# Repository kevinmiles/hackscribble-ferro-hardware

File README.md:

Hackscribble FRAM Hardware
==========================

#### *PCB designs for connecting Fujitsu MB85RS Ferroelectric memory (FRAM) to Arduino and LPCXpresso boards.*

Created on 20 April 2014 by Ray Benitez  
Last modified on 1 December 2014 by Ray Benitez		
  
These hardware designs are licensed by Ray Benitez under the Creative Commons Attribution-Sharealike 4.0 International License.
	
git@hackscribble.com | http://www.hackscribble.com | http://www.twitter.com/hackscribble

### About the hardware

#### Level converter circuits

These circuit snippets connect 3.3V MB85RS FRAM chips to 5V Arduino inputs / outputs.  

Two design approaches are shown:

1. Discrete design using BSS108 FETs, following the approach used by the Adafruit level converter.

2. Integrated design using TXB0104 to reduce PCB space required. 

The designs are in Eagle format.

#### Mini-shield

The mini-shield allows up to three 3.3V FRAMS to be connected to an Arduino (or an LPCXPresso board).  It uses an extended version of the integrated circuit snippet (above) using a TXB0108. The board has been tested with Arduino Uno and LPCXpresso 11U68 boards.

The design is in KiCad format.

The supply voltage for the Arduino / LPCXpresso side of the level converter is taken from the IOREF output of the Arduino / LPCXpresso.  This automatically adjusts for 3.3V or 5V boards.

The REVISION B board also includes test points for monitoring the SPI bus.
<br>

<hr>

### Change history

#### 1 December 2014

Added mini-shield REVISION C "slim" version.

#### 5 November 2014

Upgraded mini-shield to REVISION B.

#### 1 November 2014

Added mini-shield REVISION A.

#### 20 April 2014

Initial release of level converter circuits REVISION A.

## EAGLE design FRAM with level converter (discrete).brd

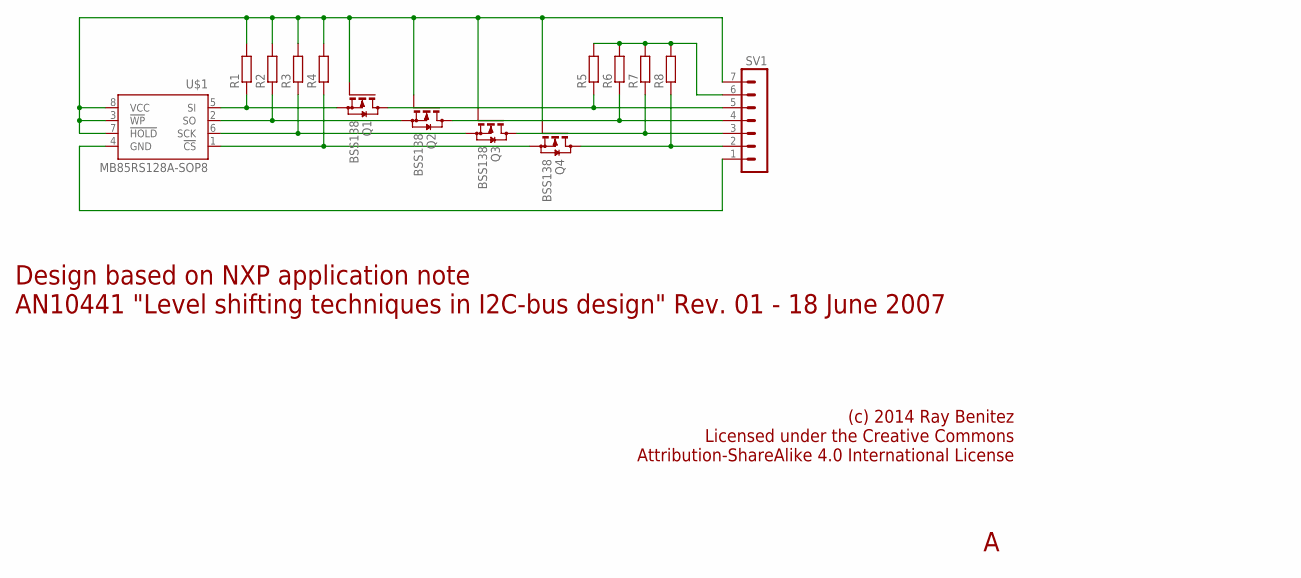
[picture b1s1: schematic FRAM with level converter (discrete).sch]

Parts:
Q1, Q2, Q3, Q4: BSS138; SOT23
R1, R2, R3, R4, R5, R6, R7, R8: R-EU_R0805; R0805
SV1: MA07-1
U$1: MB85RS128A-SOP8; SO08

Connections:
GND: SV1.1, U$1.4 (GND)
unnamed: Q1.2 (S), R1.1, U$1.5 (SI)
unnamed: Q2.2 (S), R2.1, U$1.2 (SO)
unnamed: Q3.2 (S), R3.1, U$1.6 (SCK)
unnamed: Q4.2 (S), R4.1, U$1.1 (!CS)
unnamed: Q1.1 (G), Q2.1 (G), Q3.1 (G), Q4.1 (G), R1.2, R2.2, R3.2, R4.2, SV1.7, U$1.3 (!WP), U$1.7 (!HOLD), U$1.8 (VCC)
unnamed: Q4.3 (D), R8.1, SV1.2
unnamed: Q3.3 (D), R7.1, SV1.3
unnamed: Q2.3 (D), R6.1, SV1.4
unnamed: Q1.3 (D), R5.1, SV1.5
unnamed: R5.2, R6.2, R7.2, R8.2, SV1.6

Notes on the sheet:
(c) 2014 Ray Benitez Licensed under the Creative Commons Attribution-ShareAlike 4.0 International License
Design based on NXP application note AN10441 "Level shifting techniques in I2C-bus design" Rev. 01 - 18 June 2007

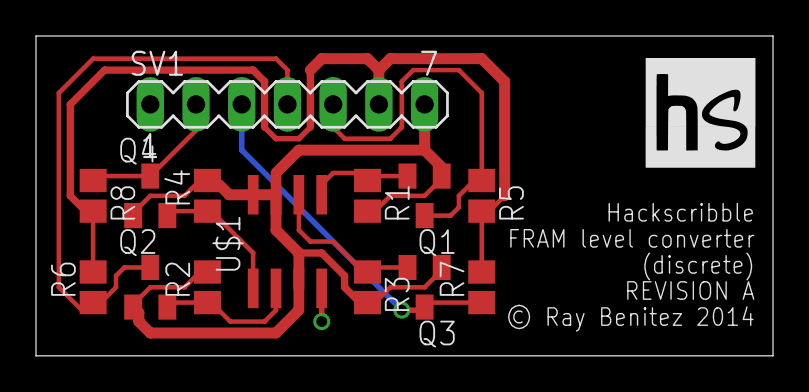
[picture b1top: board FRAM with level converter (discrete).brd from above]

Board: 2 copper layers, 40.9 x 17.8 mm, 14 parts (0 on the bottom side), 11 nets.

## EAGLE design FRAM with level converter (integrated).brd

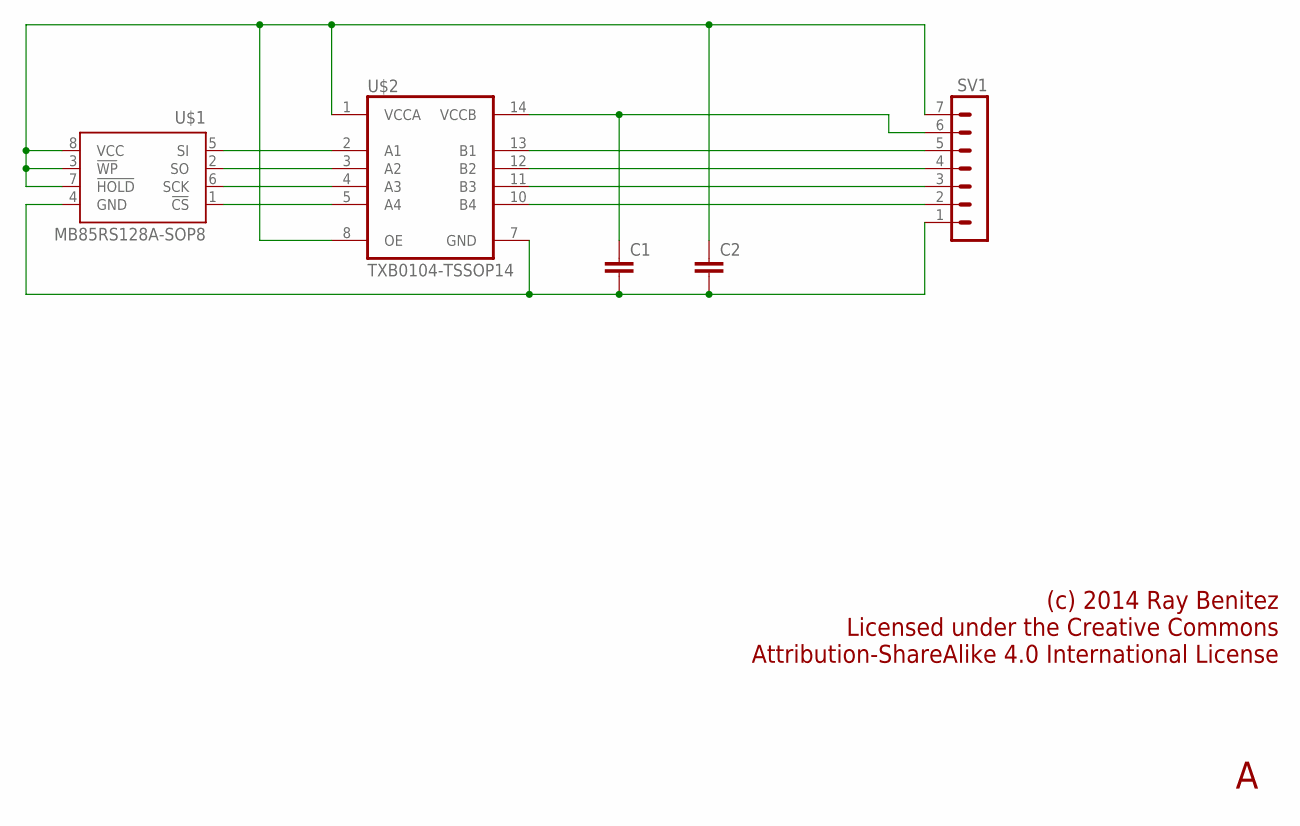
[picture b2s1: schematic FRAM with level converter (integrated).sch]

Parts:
C1, C2: C-EUC0805; C0805
SV1: MA07-1
U$1: MB85RS128A-SOP8; SO08
U$2: TXB0104-TSSOP14; TSSOP14

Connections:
GND: C1.2, C2.2, SV1.1, U$1.4 (GND), U$2.7 (GND)
unnamed: SV1.5, U$2.13 (B1)
unnamed: SV1.4, U$2.12 (B2)
unnamed: U$1.5 (SI), U$2.2 (A1)
unnamed: U$1.2 (SO), U$2.3 (A2)
unnamed: C2.1, SV1.7, U$1.3 (!WP), U$1.7 (!HOLD), U$1.8 (VCC), U$2.1 (VCCA), U$2.8 (OE)
unnamed: SV1.2, U$2.10 (B4)
unnamed: SV1.3, U$2.11 (B3)
unnamed: U$1.6 (SCK), U$2.4 (A3)
unnamed: U$1.1 (!CS), U$2.5 (A4)
unnamed: C1.1, SV1.6, U$2.14 (VCCB)

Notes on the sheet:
(c) 2014 Ray Benitez Licensed under the Creative Commons Attribution-ShareAlike 4.0 International License

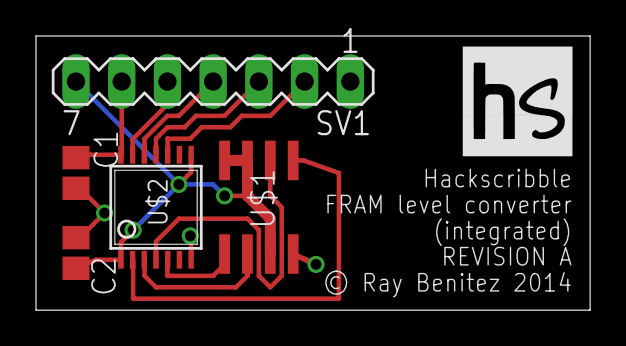
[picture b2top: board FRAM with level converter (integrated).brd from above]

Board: 2 copper layers, 30.8 x 15.2 mm, 5 parts (0 on the bottom side), 11 nets.

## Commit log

2014-04-28 Revision A.
2014-04-28 Creating first version of gh-pages.
2014-04-28 Adding content for Revision A.
2014-11-01 2014-11-01 release.
2014-11-01 Working on updates for mini-shield.
2014-11-01 Updated for release of mini-shield.
2014-11-05 2014-11-05 release.
2014-11-05 Updated README for 2014-11-05 release.
2014-11-05 Updated.
2014-12-02 2014-12-02 release.
2014-12-02 Updated for 2014-12-02 release.

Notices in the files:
FRAM with level converter (discrete).brd:
© Ray Benitez 2014
